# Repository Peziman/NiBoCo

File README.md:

# NiBoCo
Boardcomputer and controller for a CWA pump for my Nissan Micra GA16DE project

# Why
I installed a GA16DE engine from a Nissan Almera in a Nissan Micra K11 1.0. Since this engine is much larger, there was no room for the V-belt drive of the water pump. Cutting out the frame was not an option for me, so the cooling system had to be converted to an electric pump. I chose a Pierburg CWA200 water pump, which is installed in some BMWs.

I also wanted to have an additional display in my speedometer for my Speeduino.
MielArrojado's project "speeduino-ardugauge" is just perfect.

https://github.com/MielArrojado/speeduino-ardugauge

So why not combine the two?

**This is a standalone version! There's no connection to Speeduino!**

# How is the cooling system set up?

Since there was no room for the belt drive of the water pump due to space constraints, and cutting into the frame for legal reasons was avoided, an electric coolant pump from BMW, an external thermostat from a Fiat 126, and a VW secondary pump for the heating circuit are used.

The system is controlled by an Arduino Nano and a bit of chicken feed.

The CWA200 main pump is controlled via a PWM (pulse width modulation) signal.
The secondary pump is also controlled via a PWM signal.

The speed and the corresponding flow rate are regulated directly by the coolant temperature. Visual feedback is provided via a display and an RGB LED in the instrument cluster. The control points can be adjusted using two potentiometers.

The radiator fan is also controlled by the controller.

# How is it regulated?

Temperature control is achieved via a total of 4 different temperature programs,
which are referred to as modes below. The currently active mode is indicated by the LED in the instrument cluster.

The system regulates to a target temperature (e.g., 85°C).

### Mode 1 (Warm-Up Pulse Mode)

If the coolant temperature is less than 25°C below the target temperature (60°C), the engine speed switches between an absolute minimum value of 10% (350 rpm) and the predefined lower reference point, which is set via the "Reference Low" potentiometer (e.g., 30%).

The pump then runs for 30 seconds at 10% speed and 4 seconds at 30% speed.

The secondary pump runs at approximately 60% speed.

This ensures a clean and rapid warm-up of the engine.

As feedback, the LED in the instrument cluster illuminates blue.

### Mode 2 (Warm-Up)

When the coolant temperature is between 25°C and 10°C below the target temperature (60°C-75°C), the pump speed is maintained at the predefined lower reference point.

The secondary pump is continuously ramped up to 100%.

As feedback, the LED in the instrument cluster lights up turquoise.

### Mode 3 (Normal Operation)

When the coolant temperature is higher than 10°C below the target temperature, the pump speed is controlled by a PID-styled controller.

The maximum operating speed can be set using the potentiometer "Reference High" (e.g., 90%).

The PID controller attempts to maintain the temperature at 85°C by adjusting the pump speed.

The secondary pump continues to run at 100%.

As feedback, the LED in the instrument cluster lights up green.

### Mode 4 (Overheating)

If the coolant temperature exceeds 98°C (target temperature +13°C), the speed of
both pumps is set to 100% to counteract further overheating.

This pump behavior also occurs if the connection to the pump is interrupted. (Fail-Safe Mode)
As feedback, the LED in the instrument cluster lights up red.

## Fan Control
At a set temperature of 90°C, the radiator fan is activated.

The hysteresis is 4°C.

## Afterrun control

When the ignition is switched off, the pump does not switch off immediately but continues to monitor the coolant temperature.

If the temperature is within the Mode 3 range, the pump continues to run for another 60 seconds to prevent potential hot spots in the engine.

# What else can it do?

The display also shows water temperature, oil temperature, vehicle voltage, pump status, and a few bit indicators.

It's located in the instrument cluster in place of the clock.

Operation is via three pushbuttons, which were originally intended for the clock (forward, back, enter).

The display has the following pages:

### Page 1:

Oil and water temperature display

### Page 2:

Vehicle voltage display

### Page 3:

Main pump status, such as setpoints, current speed, etc.

### Page 4:

Various indicators, such as fan running, after-run active, sensor fault, etc.

### Page 5:

Auxiliary pump status, such as setpoints, current speed, etc.

### Page 6:
Frames per second

Additionally, alarm messages are displayed when limit values ​​are exceeded.

By pressing and holding the Enter key, you can switch to a kind of test mode to manually control the pumps and fans.

# What's next?

Since this project has been working flawlessly in my car for 1.5 years, I consider it complete.

I might add an oil pressure sensor, but will that ever happen? We'll see what the future holds.

Feel free to build your own.

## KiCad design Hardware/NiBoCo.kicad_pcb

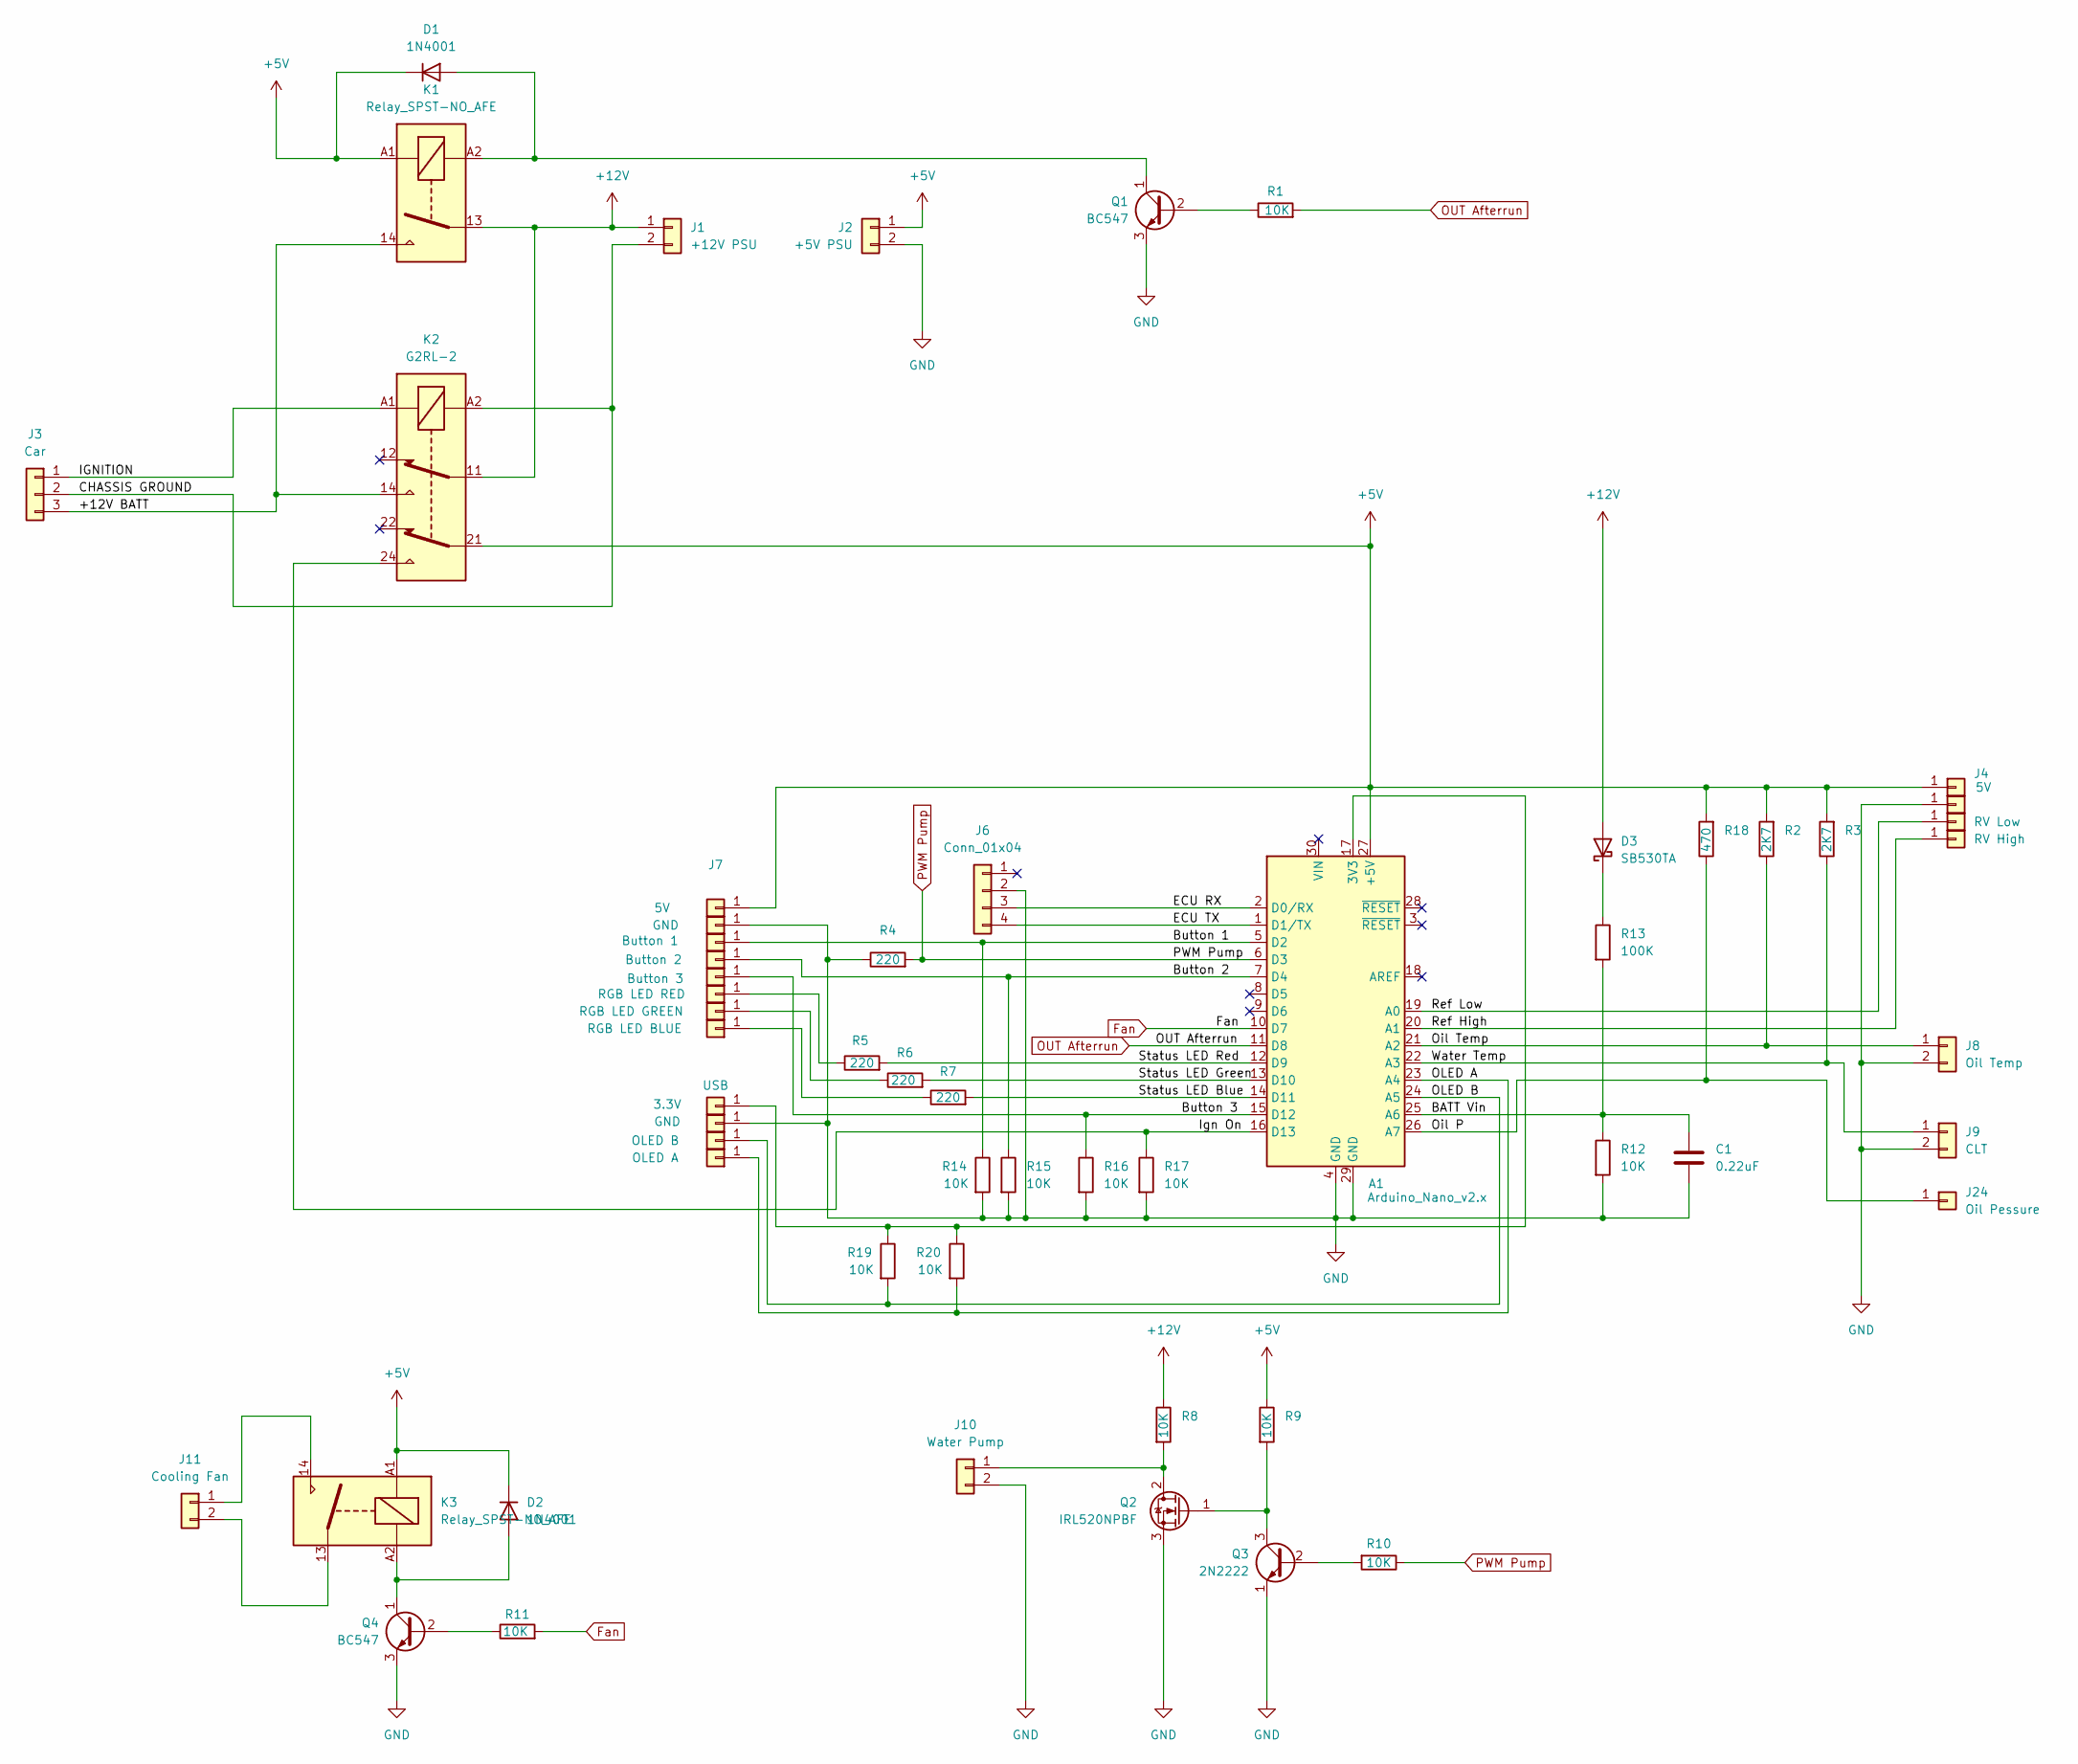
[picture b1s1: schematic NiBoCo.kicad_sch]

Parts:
A1: Arduino_Nano_v2.x; Arduino_Nano
C1: 0.22uF; C_Rect_L4.6mm_W4.6mm_P2.50mm_MKS02_FKP02
D1, D2: 1N4001; D_DO-41_SOD81_P10.16mm_Horizontal
D3: SB530TA; D_DO-201AD_P15.24mm_Horizontal
J1: +12V PSU; JST_NV_B02P-NV_1x02_P5.00mm_Vertical
J2: +5V PSU; JST_NV_B02P-NV_1x02_P5.00mm_Vertical
J3: Car; JST_NV_B03P-NV_1x03_P5.00mm_Vertical
J4, J7: 5V; TestPoint_Loop_D2.60mm_Drill1.4mm_Beaded
J5, J14, J21: GND; TestPoint_Loop_D2.60mm_Drill1.4mm_Beaded
J6: Conn_01x04; JST_NV_B04P-NV_1x04_P5.00mm_Vertical
J8: Oil Temp; JST_NV_B02P-NV_1x02_P5.00mm_Vertical
J9: CLT; JST_NV_B02P-NV_1x02_P5.00mm_Vertical
J10: Water Pump; JST_NV_B02P-NV_1x02_P5.00mm_Vertical
J11: Cooling Fan; JST_NV_B02P-NV_1x02_P5.00mm_Vertical
J12: RV Low; TestPoint_Loop_D2.60mm_Drill1.4mm_Beaded
J13: RV High; TestPoint_Loop_D2.60mm_Drill1.4mm_Beaded
J15: Button 1; TestPoint_Loop_D2.60mm_Drill1.4mm_Beaded
J16: Button 2; TestPoint_Loop_D2.60mm_Drill1.4mm_Beaded
J17: Button 3; TestPoint_Loop_D2.60mm_Drill1.4mm_Beaded
J18: RGB LED RED; TestPoint_Loop_D2.60mm_Drill1.4mm_Beaded
J19: RGB LED GREEN; TestPoint_Loop_D2.60mm_Drill1.4mm_Beaded
J20: RGB LED BLUE; TestPoint_Loop_D2.60mm_Drill1.4mm_Beaded
J22: OLED B; TestPoint_Loop_D2.60mm_Drill1.4mm_Beaded
J23: OLED A; TestPoint_Loop_D2.60mm_Drill1.4mm_Beaded
J24: Oil Pessure
K1, K3: Relay_SPST-NO_AFE; Relay_SPST_Zettler-AZSR131
K2: G2RL-2; Relay_DPDT_Omron_G2RL-2
Q1, Q4: BC547; TO-92_Inline
Q2: IRL520NPBF; TO-220-3_Vertical
Q3: 2N2222; TO-39-3
R1, R8, R9, R10, R11, R12, R14, R15, R16, R17, R19, R20: 10K; R_Axial_DIN0204_L3.6mm_D1.6mm_P5.08mm_Horizontal
R2, R3: 2K7; R_Axial_DIN0204_L3.6mm_D1.6mm_P5.08mm_Horizontal
R4, R5, R6, R7: 220; R_Axial_DIN0204_L3.6mm_D1.6mm_P5.08mm_Horizontal
R13: 100K; R_Axial_DIN0204_L3.6mm_D1.6mm_P5.08mm_Horizontal
R18: 470; R_Axial_DIN0204_L3.6mm_D1.6mm_P5.08mm_Horizontal
USB: 3.3V; TestPoint_Loop_D2.60mm_Drill1.4mm_Beaded

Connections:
+5V: A1.27 (+5V), D1.1 (K), D2.1 (K), J2.1, J4.1, J7.1, K1.A1, K2.21, K3.A1, R2.2, R3.2, R9.1, R18.2
+12V: D3.2 (A), J1.1, K1.13, K2.11, R8.1
/+12V BATT: J3.3, K1.14, K2.14
/BATT Vin: A1.25 (A6), C1.1, R12.1, R13.2
/Button 1: A1.5 (D2), J15.1, R14.1
/Button 2: A1.7 (D4), J16.1, R15.1
/Button 3: A1.15 (D12), J17.1, R16.1
/CHASSIS GROUND: J1.2, J3.2, K2.A2
/ECU RX: A1.2 (D0/RX), J6.3
/ECU TX: A1.1 (D1/TX), J6.4
/IGNITION: J3.1, K2.A1
/Ign On: A1.16 (D13), K2.24, R17.1
/OLED A: A1.23 (A4), J23.1, R20.2
/OLED B: A1.24 (A5), J22.1, R19.2
/Oil Temp: A1.21 (A2), J8.1, R2.1
/Ref High: A1.20 (A1), J13.1
/Ref Low: A1.19 (A0), J12.1
/Status LED Blue: A1.14 (D11), R7.2
/Status LED Green: A1.13 (D10), R6.2
/Status LED Red: A1.12 (D9), R5.2
/Water Temp: A1.22 (A3), J9.1, R3.1
Fan: A1.10 (D7), R11.2
GND: A1.4 (GND), A1.29 (GND), C1.2, J2.2, J5.1, J6.2, J8.2, J9.2, J10.2, J14.1, J21.1, Q1.3 (E), Q2.3 (S), Q3.1 (E), Q4.3 (E), R4.1, R12.2, R14.2, R15.2, R16.2, R17.2
unnamed: D1.2 (A), K1.A2, Q1.1 (C)
unnamed: D2.2 (A), K3.A2, Q4.1 (C)
unnamed: D3.1 (K), R13.1
unnamed: J10.1, Q2.2 (D), R8.2
unnamed: J11.1, K3.14
unnamed: J11.2, K3.13
unnamed: J18.1, R5.1
unnamed: J19.1, R6.1
unnamed: J20.1, R7.1
unnamed: A1.26 (A7), J24.1, R18.1
unnamed: Q1.2 (B), R1.1
unnamed: Q2.1 (G), Q3.3 (C), R9.2
unnamed: Q3.2 (B), R10.2
unnamed: Q4.2 (B), R11.1
unnamed: A1.17 (3V3), R19.1, R20.1, USB.1
OUT Afterrun: A1.11 (D8), R1.2
PWM Pump: A1.6 (D3), R4.2, R10.1

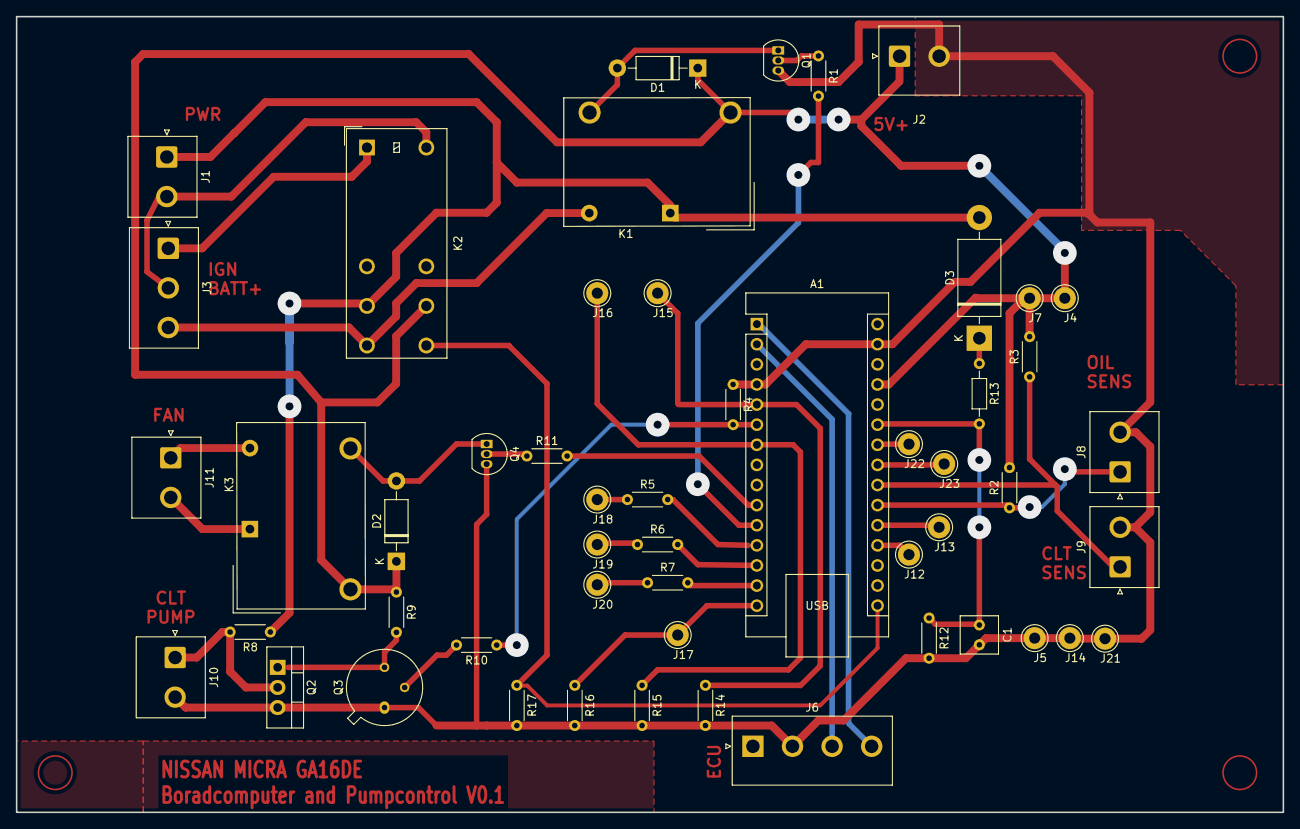
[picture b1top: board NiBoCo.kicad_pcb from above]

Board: 2 copper layers, 160.0 x 100.5 mm, 52 parts (0 on the bottom side), 38 nets.

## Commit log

2024-11-12 Rename IMG_20240529_221358.jpg to MEDIA/CWA200.jpg
2024-11-12 Rename CWA200.jpg to MEDIA/CWA200.jpg
2026-01-16 Rename Diagramm Pumpenregelung.jpg to Diagramm_Pumpenregelung.jpg
2026-01-16 Delete MEDIA/Tachometer.jpg
    tooooo big
2026-01-21 Create Tools
